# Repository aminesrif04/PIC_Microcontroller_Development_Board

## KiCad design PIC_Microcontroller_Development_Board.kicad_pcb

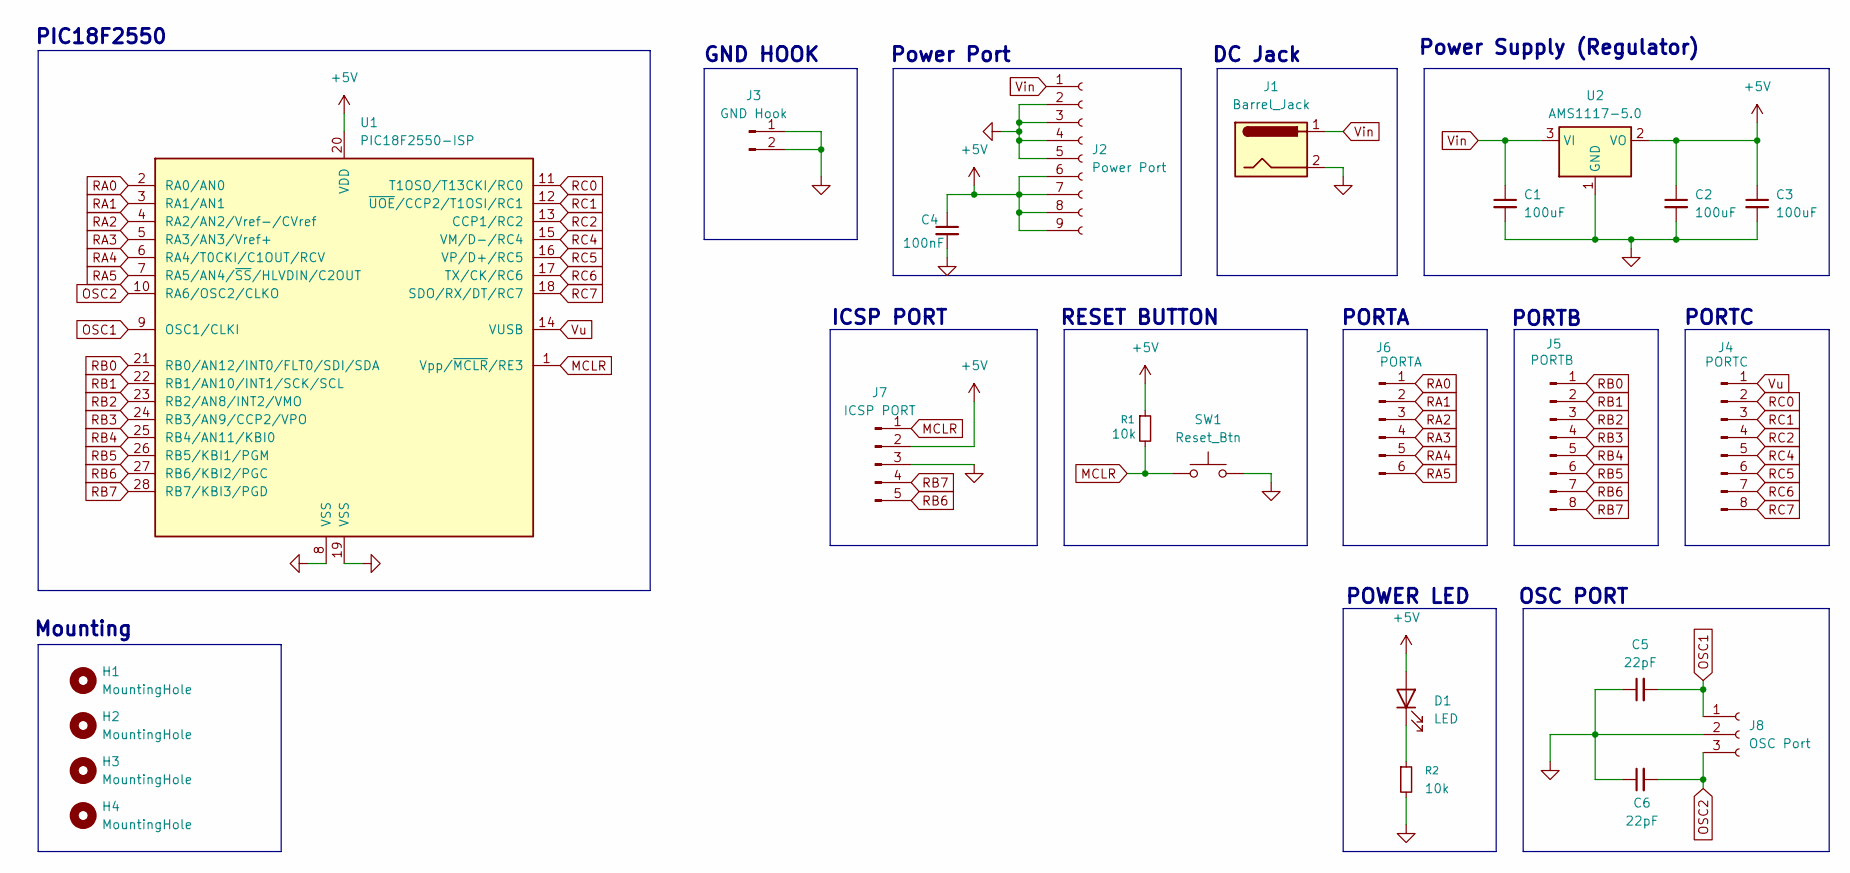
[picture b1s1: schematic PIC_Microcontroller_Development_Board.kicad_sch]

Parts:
C1, C2, C3: 100uF; CP_Radial_D4.0mm_P2.00mm
C4: 100nF; C_Disc_D3.0mm_W1.6mm_P2.50mm
C5, C6: 22pF; C_Disc_D3.0mm_W1.6mm_P2.50mm
D1: LED; LED_D3.0mm
H1, H2, H3, H4: MountingHole; MountingHole_2.1mm
J1: Barrel_Jack; BarrelJack_Horizontal
J2: Power Port; PinSocket_1x09_P2.54mm_Vertical
J3: GND Hook; PinHeader_1x02_P2.54mm_Vertical
J4: PORTC; PinSocket_1x08_P2.54mm_Vertical
J5: PORTB; PinSocket_1x08_P2.54mm_Vertical
J6: PORTA; PinSocket_1x06_P2.54mm_Vertical
J7: ICSP PORT; PinSocket_1x05_P2.54mm_Vertical
J8: OSC Port; PinSocket_1x03_P2.54mm_Vertical
R1, R2: 10k; R_Axial_DIN0204_L3.6mm_D1.6mm_P5.08mm_Horizontal
SW1: Reset_Btn; SW_SPST_TS-1088-xR025
U1: PIC18F2550-ISP; DIP-28_W7.62mm
U2: AMS1117-5.0; SOT-223-3_TabPin2

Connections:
+5V: C2.1, C3.1, C4.1, D1.2 (A), J2.6, J2.7, J2.8, J2.9, J7.2, R1.1, U1.20 (VDD), U2.2 (VO)
GND: C1.2, C2.2, C3.2, C4.2, C5.1, C6.1, J1.2, J2.2, J2.3, J2.4, J2.5, J3.1, J3.2, J7.3, J8.2, R2.2, SW1.2, U1.8 (VSS), U1.19 (VSS), U2.1 (GND)
MCLR: J7.1, R1.2, SW1.1, U1.1 (Vpp/~MCLR/RE3)
unnamed: D1.1 (K), R2.1
OSC1: C5.2, J8.1, U1.9 (OSC1/CLKI)
OSC2: C6.2, J8.3, U1.10 (RA6/OSC2/CLKO)
RA0: J6.1, U1.2 (RA0/AN0)
RA1: J6.2, U1.3 (RA1/AN1)
RA2: J6.3, U1.4 (RA2/AN2/Vref-/CVref)
RA3: J6.4, U1.5 (RA3/AN3/Vref+)
RA4: J6.5, U1.6 (RA4/T0CKI/C1OUT/RCV)
RA5: J6.6, U1.7 (RA5/AN4/~SS/HLVDIN/C2OUT)
RB0: J5.1, U1.21 (RB0/AN12/INT0/FLT0/SDI/SDA)
RB1: J5.2, U1.22 (RB1/AN10/INT1/SCK/SCL)
RB2: J5.3, U1.23 (RB2/AN8/INT2/VMO)
RB3: J5.4, U1.24 (RB3/AN9/CCP2/VPO)
RB4: J5.5, U1.25 (RB4/AN11/KBI0)
RB5: J5.6, U1.26 (RB5/KBI1/PGM)
RB6: J5.7, J7.5, U1.27 (RB6/KBI2/PGC)
RB7: J5.8, J7.4, U1.28 (RB7/KBI3/PGD)
RC0: J4.2, U1.11 (T1OSO/T13CKI/RC0)
RC1: J4.3, U1.12 (~UOE/CCP2/T1OSI/RC1)
RC2: J4.4, U1.13 (CCP1/RC2)
RC4: J4.5, U1.15 (VM/D-/RC4)
RC5: J4.6, U1.16 (VP/D+/RC5)
RC6: J4.7, U1.17 (TX/CK/RC6)
RC7: J4.8, U1.18 (SDO/RX/DT/RC7)
Vin: C1.1, J1.1, J2.1, U2.3 (VI)
Vu: J4.1, U1.14 (VUSB)

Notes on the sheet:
PORTC
DC Jack
RESET BUTTON
ICSP PORT
PORTA
POWER LED
Mounting
PIC18F2550
GND HOOK
OSC PORT
Power Port
PORTB
Power Supply (Regulator)

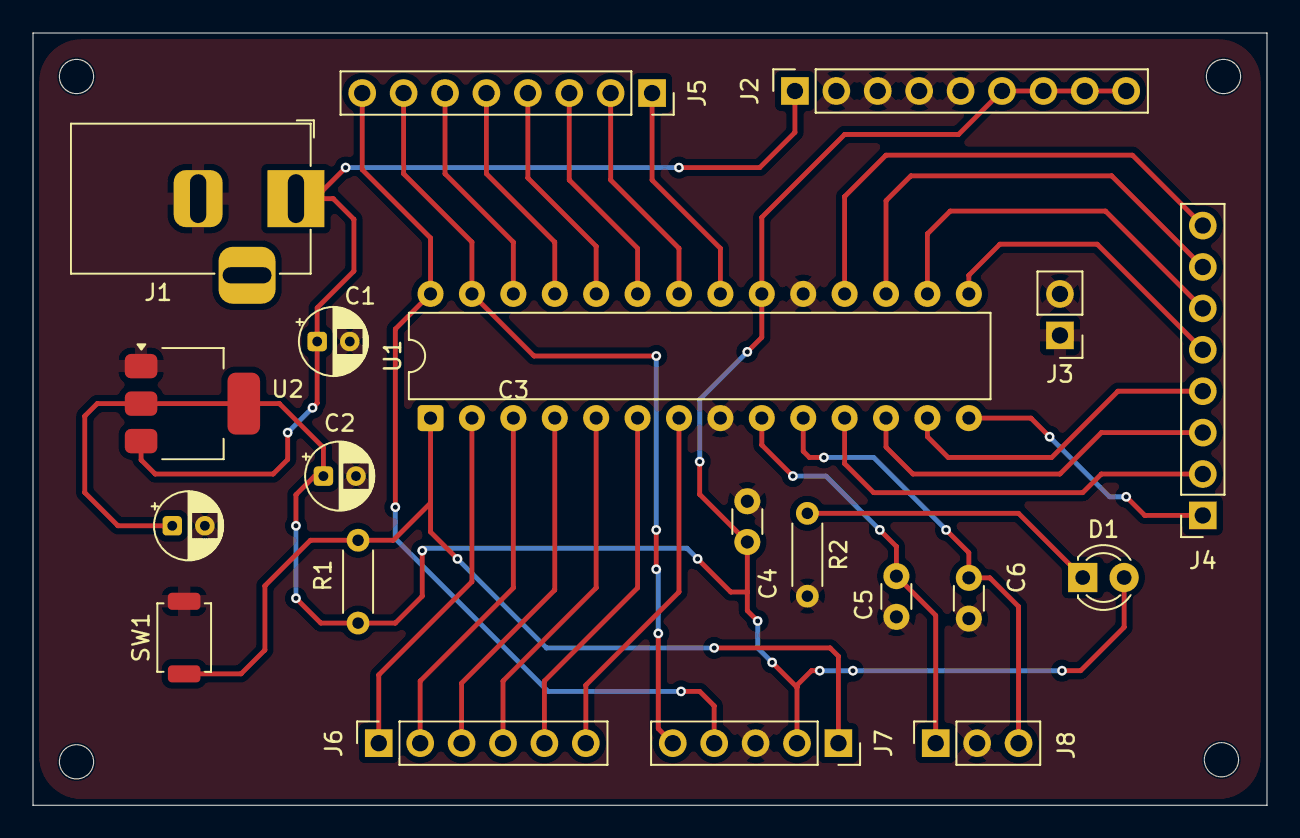
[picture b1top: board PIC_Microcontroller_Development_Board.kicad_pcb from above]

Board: 2 copper layers, 75.7 x 47.4 mm, 24 parts (0 on the bottom side), 29 nets.
